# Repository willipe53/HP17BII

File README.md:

# HP17BII

This is a project done to test several microcontrollers by using them to replace the innards of an HP 17BII business calculator with several new functions, such as Space Invaders game, a piano, and yes of course also hand-coded calculator. 

All attempts are included here.  Probably the most complete version is [HP17B41.ino](HP17B41/HP17B41.ino), though it might take a little work to get any of these to compile at this point.  I only make public because others may wish to replicate some of the functionality below.

`#define PIANO_MODE` renders a piano on the display, then plays notes on the HP's piezo buzzer.  The buzzer is connected to an analog pin, and when a piano key is pressed, the desired frequemcy is tossed into an array (two arrays actually: `toneStart[]` for the start time in millis and `toneFreq[]` for the frequency) to be read and played by the main loop.

`#define GAME_MODE` is the Space Invaders game.  If I come back to this, I'll probably make it a lot more object-oriented.  This version is anything but that.  It relies on a lot of global variables such as `goingLeft`, `goingRight`, `gunX`, `gunY`, `alienX`, `alienY`, and others to figure out where to place the gun and the aliens, whether a bullet has been fired, and the state of the barriers that the gun hides behind.  The hard work is done in a function called `drawPlayArea()` that is called by the main loop.
   
`#define CALC_MODE` is the default mode, the calculator.  It is a bit over-engineered with a really hard to understand function pointer array which is called by main: 

`(*fcns[key][currentMode]) (key);` 

whenever a key press event is detected by the `<Keypad.h>` library.  

Most of this code needs to be rewritten, to be honest.  I only make this project public because there may be useful code snippets for people challenging themselves with similar microcontroller display and sound challenges.

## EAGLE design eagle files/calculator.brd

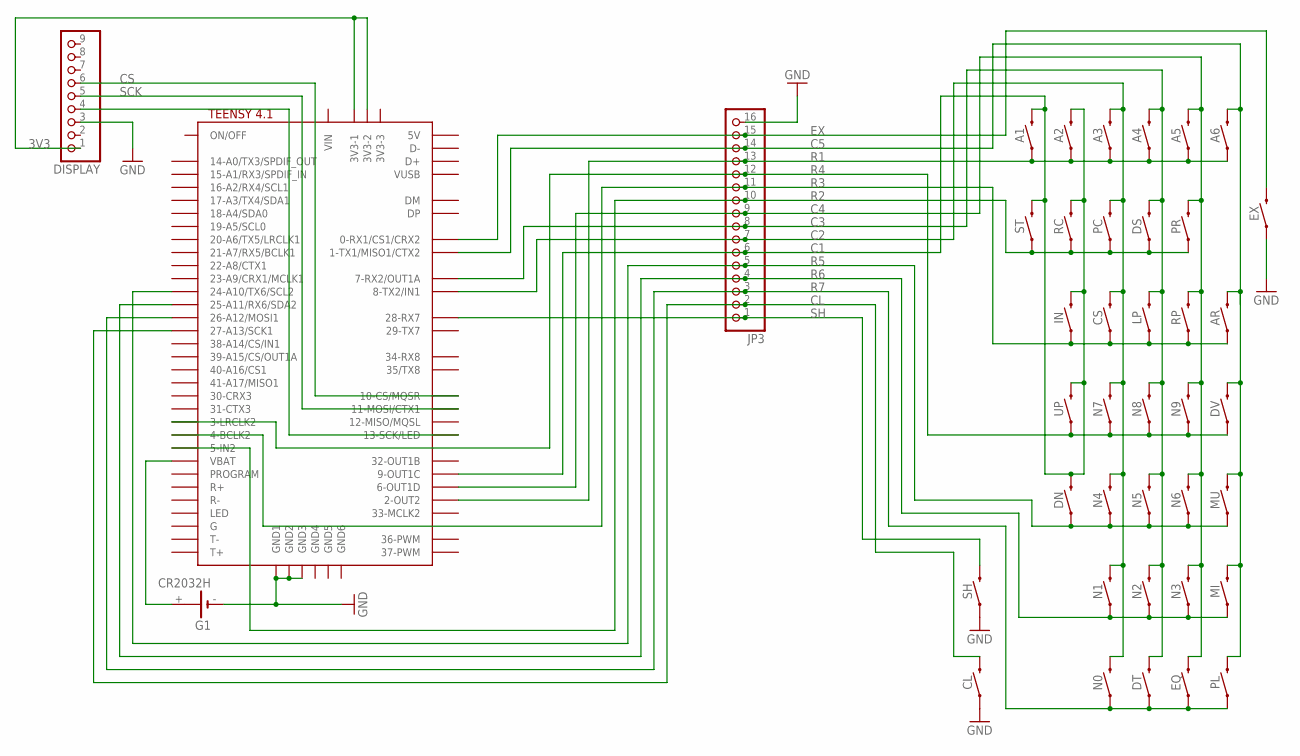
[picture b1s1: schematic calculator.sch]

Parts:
A1, A2, A3, A4, A5, A6: MOMENTARY-SWITCH-SPST-PTH-6.0MM; TACTILE_SWITCH_PTH_6.0MM
AR: MOMENTARY-SWITCH-SPST-PTH-6.0MM; TACTILE_SWITCH_PTH_6.0MM
CL: MOMENTARY-SWITCH-SPST-PTH-6.0MM; TACTILE_SWITCH_PTH_6.0MM
CS: MOMENTARY-SWITCH-SPST-PTH-6.0MM; TACTILE_SWITCH_PTH_6.0MM
DISPLAY: PINHD-1X9; 1X09-BIG
DN: MOMENTARY-SWITCH-SPST-PTH-6.0MM; TACTILE_SWITCH_PTH_6.0MM
DS: MOMENTARY-SWITCH-SPST-PTH-6.0MM; TACTILE_SWITCH_PTH_6.0MM
DT: MOMENTARY-SWITCH-SPST-PTH-6.0MM; TACTILE_SWITCH_PTH_6.0MM
DV: MOMENTARY-SWITCH-SPST-PTH-6.0MM; TACTILE_SWITCH_PTH_6.0MM
EQ: MOMENTARY-SWITCH-SPST-PTH-6.0MM; TACTILE_SWITCH_PTH_6.0MM
EX: MOMENTARY-SWITCH-SPST-PTH-6.0MM; TACTILE_SWITCH_PTH_6.0MM
G1: CR2032H
IN: MOMENTARY-SWITCH-SPST-PTH-6.0MM; TACTILE_SWITCH_PTH_6.0MM
JP3: PINHD-1X16; 1X16
LP: MOMENTARY-SWITCH-SPST-PTH-6.0MM; TACTILE_SWITCH_PTH_6.0MM
MI: MOMENTARY-SWITCH-SPST-PTH-6.0MM; TACTILE_SWITCH_PTH_6.0MM
MU: MOMENTARY-SWITCH-SPST-PTH-6.0MM; TACTILE_SWITCH_PTH_6.0MM
N0, N1, N2, N3, N4, N5, N6, N7, N8, N9: MOMENTARY-SWITCH-SPST-PTH-6.0MM; TACTILE_SWITCH_PTH_6.0MM
PC: MOMENTARY-SWITCH-SPST-PTH-6.0MM; TACTILE_SWITCH_PTH_6.0MM
PL: MOMENTARY-SWITCH-SPST-PTH-6.0MM; TACTILE_SWITCH_PTH_6.0MM
PR: MOMENTARY-SWITCH-SPST-PTH-6.0MM; TACTILE_SWITCH_PTH_6.0MM
RC: MOMENTARY-SWITCH-SPST-PTH-6.0MM; TACTILE_SWITCH_PTH_6.0MM
RP: MOMENTARY-SWITCH-SPST-PTH-6.0MM; TACTILE_SWITCH_PTH_6.0MM
SH: MOMENTARY-SWITCH-SPST-PTH-6.0MM; TACTILE_SWITCH_PTH_6.0MM
ST: MOMENTARY-SWITCH-SPST-PTH-6.0MM; TACTILE_SWITCH_PTH_6.0MM
U$1: TEENSY41
UP: MOMENTARY-SWITCH-SPST-PTH-6.0MM; TACTILE_SWITCH_PTH_6.0MM

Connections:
3V3: DISPLAY.1, U$1.3V3-1, U$1.3V3-2
C1: A1.3 (2), A2.3 (2), DN.3 (2), IN.3 (2), JP3.6, RC.3 (2), ST.3 (2), U$1.9-OUT1C, UP.3 (2)
C2: A3.3 (2), CS.3 (2), JP3.7, N0.3 (2), N1.3 (2), N4.3 (2), N7.3 (2), PC.3 (2), U$1.8-TX2/IN2 (8-TX2/IN1)
C3: A4.3 (2), DS.3 (2), DT.3 (2), JP3.8, LP.3 (2), N2.3 (2), N5.3 (2), N8.3 (2), U$1.7-RX2/OUT1A
C4: A5.3 (2), EQ.3 (2), JP3.9, N3.3 (2), N6.3 (2), N9.3 (2), PR.3 (2), RP.3 (2), U$1.6-OUT1D
C5: A6.3 (2), AR.3 (2), DV.3 (2), JP3.14, MI.3 (2), MU.3 (2), PL.3 (2), U$1.1-TX1/MISO1/CTX2
CL: CL.3 (2), JP3.2, U$1.27-A13/SCK1
CS: DISPLAY.6, U$1.10-CS\MQSR (10-CS/MQSR)
EX: EX.3 (2), JP3.15, U$1.0-RX1/CS1/CRX2
GND: CL.1, DISPLAY.3, EX.1, G1.-, JP3.16, SH.1, U$1.GND1, U$1.GND2, U$1.GND3
MOSI: DISPLAY.5, U$1.11-MOSI/CTX1
unnamed: G1.+, U$1.VBAT
R1: A1.1, A2.1, A3.1, A4.1, A5.1, A6.1, JP3.13, U$1.2-OUT2
R2: DS.1, JP3.10, PC.1, PR.1, RC.1, ST.1, U$1.5-IN2
R3: AR.1, CS.1, IN.1, JP3.11, LP.1, RP.1, U$1.4-BCLK2
R4: DV.1, JP3.12, N7.1, N8.1, N9.1, U$1.3-LRCLK2, UP.1
R5: DN.1, JP3.5, MU.1, N4.1, N5.1, N6.1, U$1.24-A10/TX6/SCL2
R6: JP3.4, MI.1, N1.1, N2.1, N3.1, U$1.25-A11/RX6/SDA2
R7: DT.1, EQ.1, JP3.3, N0.1, PL.1, U$1.26-A12/MOSI1
SCK: DISPLAY.4, U$1.13-SCK/LED
SH: JP3.1, SH.3 (2), U$1.28-RX7

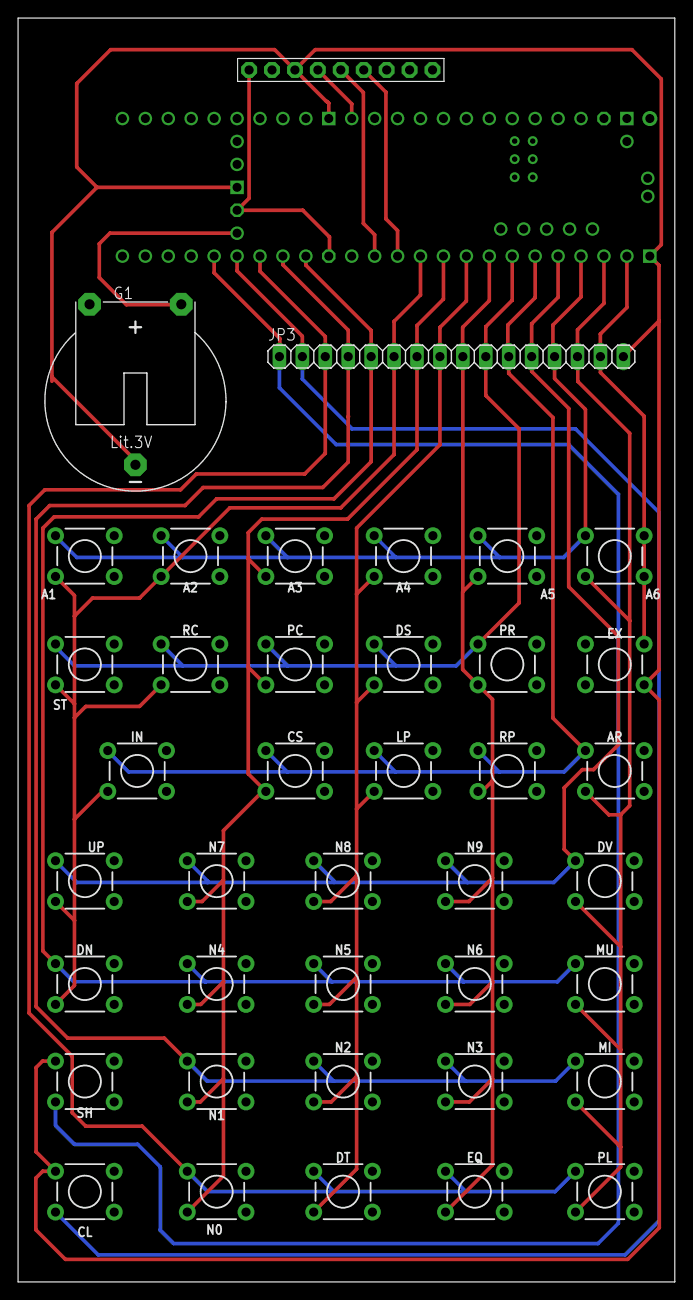
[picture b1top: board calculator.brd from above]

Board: 2 copper layers, 72.8 x 140.0 mm, 41 parts (1 on the bottom side), 21 nets.

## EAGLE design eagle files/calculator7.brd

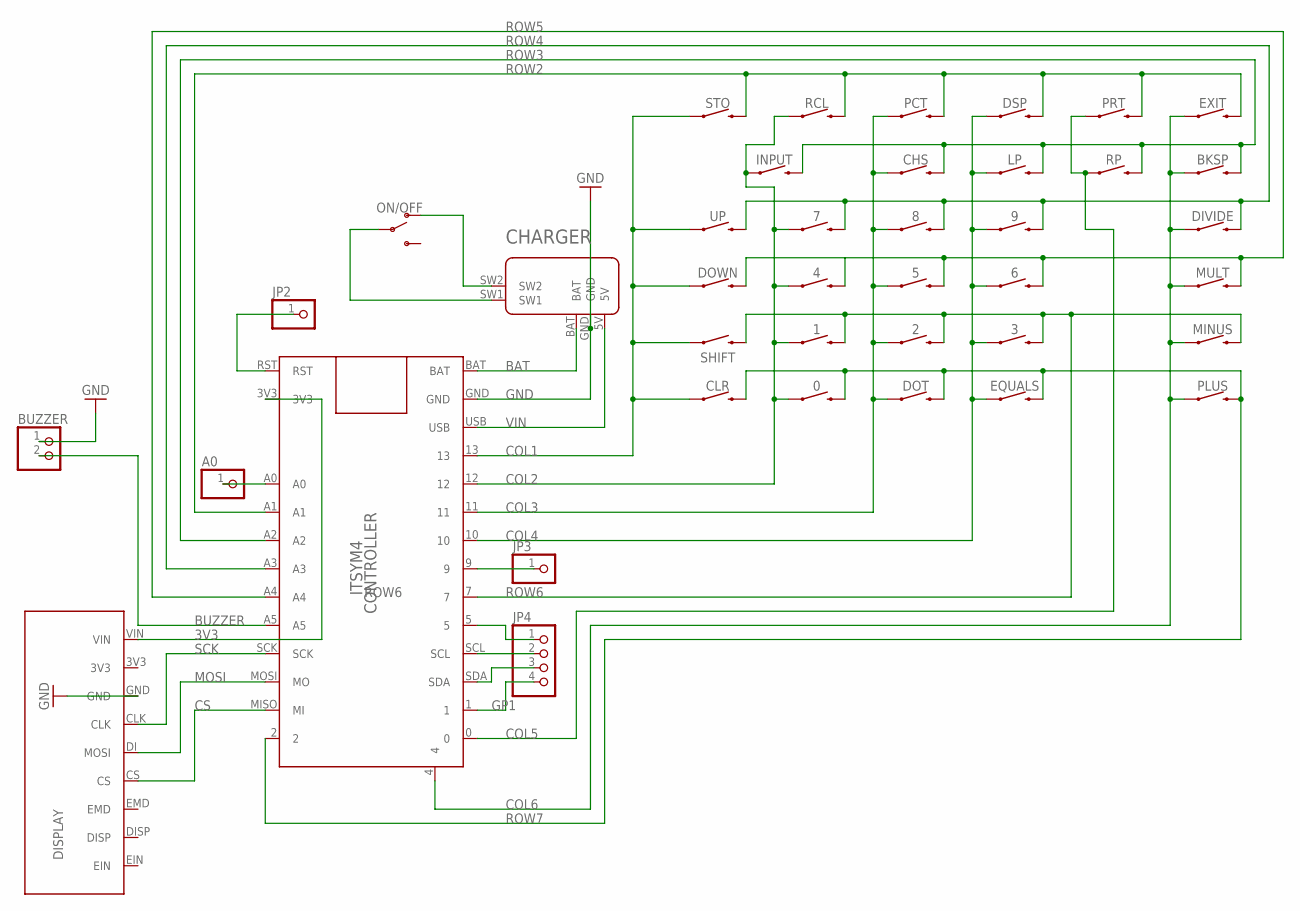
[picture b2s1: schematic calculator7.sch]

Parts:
0, 1, 2, 3, 4, 5, 6, 7, 8, 9: 3BUTTON
A0: PINHD-1X1; 1X01
BKSP: 3BUTTON
BUZZER: PINHD-1X2; 1X02
CHARGER: LIPO_BACKPACK
CHS: 3BUTTON
CLR: 3BUTTON
CONTROLLER: ITSYM4
DISPLAY: SHARPMEM_FULL
DIVIDE: 3BUTTON
DOT: 3BUTTON
DOWN: 3BUTTON
DSP: 3BUTTON
EQUALS: 3BUTTON
EXIT: 3BUTTON
INPUT: 3BUTTON
JP2, JP3: PINHD-1X1; 1X01
JP4: PINHD-1X4; 1X04
LP: 3BUTTON
MINUS: 3BUTTON
MULT: 3BUTTON
ON/OFF: LIL_SWITCH
PCT: 3BUTTON
PLUS: 3BUTTON
PRT: 3BUTTON
RCL: 3BUTTON
RP: 3BUTTON
SHIFT: 3BUTTON
STO: 3BUTTON
UP: 3BUTTON

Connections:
3V3: CONTROLLER.3V3, DISPLAY.VIN
A0: A0.1, CONTROLLER.A0
BAT: CHARGER.BAT, CONTROLLER.BAT
BUZZER: BUZZER.2, CONTROLLER.A5
COL1: CLR.P1 (1), CONTROLLER.13, DOWN.P1 (1), SHIFT.P1 (1), STO.P1 (1), UP.P1 (1)
COL2: 0.P1 (1), 1.P1 (1), 4.P1 (1), 7.P1 (1), CONTROLLER.12, INPUT.P1 (1), RCL.P1 (1)
COL3: 2.P1 (1), 5.P1 (1), 8.P1 (1), CHS.P1 (1), CONTROLLER.11, DOT.P1 (1), PCT.P1 (1)
COL4: 3.P1 (1), 6.P1 (1), 9.P1 (1), CONTROLLER.10, DSP.P1 (1), EQUALS.P1 (1), LP.P1 (1)
COL5: CONTROLLER.0, PRT.P1 (1), RP.P1 (1)
COL6: BKSP.P1 (1), CONTROLLER.4, DIVIDE.P1 (1), EXIT.P1 (1), MINUS.P1 (1), MULT.P1 (1), PLUS.P1 (1)
CS: CONTROLLER.MISO (MI), DISPLAY.CS
GND: BUZZER.1, CHARGER.GND, CONTROLLER.GND, DISPLAY.GND
GP1: CONTROLLER.1, JP4.4
GP5: CONTROLLER.5, JP4.1
GP9: CONTROLLER.9, JP3.1
MOSI: CONTROLLER.MOSI (MO), DISPLAY.DI (MOSI)
unnamed: CHARGER.SW1, ON/OFF.COM
unnamed: CHARGER.SW2, ON/OFF.P1
ROW2: CONTROLLER.A1, DSP.P2 (2), EXIT.P2 (2), PCT.P2 (2), PRT.P2 (2), RCL.P2 (2), STO.P2 (2)
ROW3: BKSP.P2 (2), CHS.P2 (2), CONTROLLER.A2, INPUT.P2 (2), LP.P2 (2), RP.P2 (2)
ROW4: 7.P2 (2), 8.P2 (2), 9.P2 (2), CONTROLLER.A3, DIVIDE.P2 (2), UP.P2 (2)
ROW5: 4.P2 (2), 5.P2 (2), 6.P2 (2), CONTROLLER.A4, DOWN.P2 (2), MULT.P2 (2)
ROW6: 1.P2 (2), 2.P2 (2), 3.P2 (2), CONTROLLER.7, MINUS.P2 (2), SHIFT.P2 (2)
ROW7: 0.P2 (2), CLR.P2 (2), CONTROLLER.2, DOT.P2 (2), EQUALS.P2 (2), PLUS.P2 (2)
RST: CONTROLLER.RST, JP2.1
SCK: CONTROLLER.SCK, DISPLAY.CLK
SCL: CONTROLLER.SCL, JP4.2
SDA: CONTROLLER.SDA, JP4.3
VIN: CHARGER.5V, CONTROLLER.USB

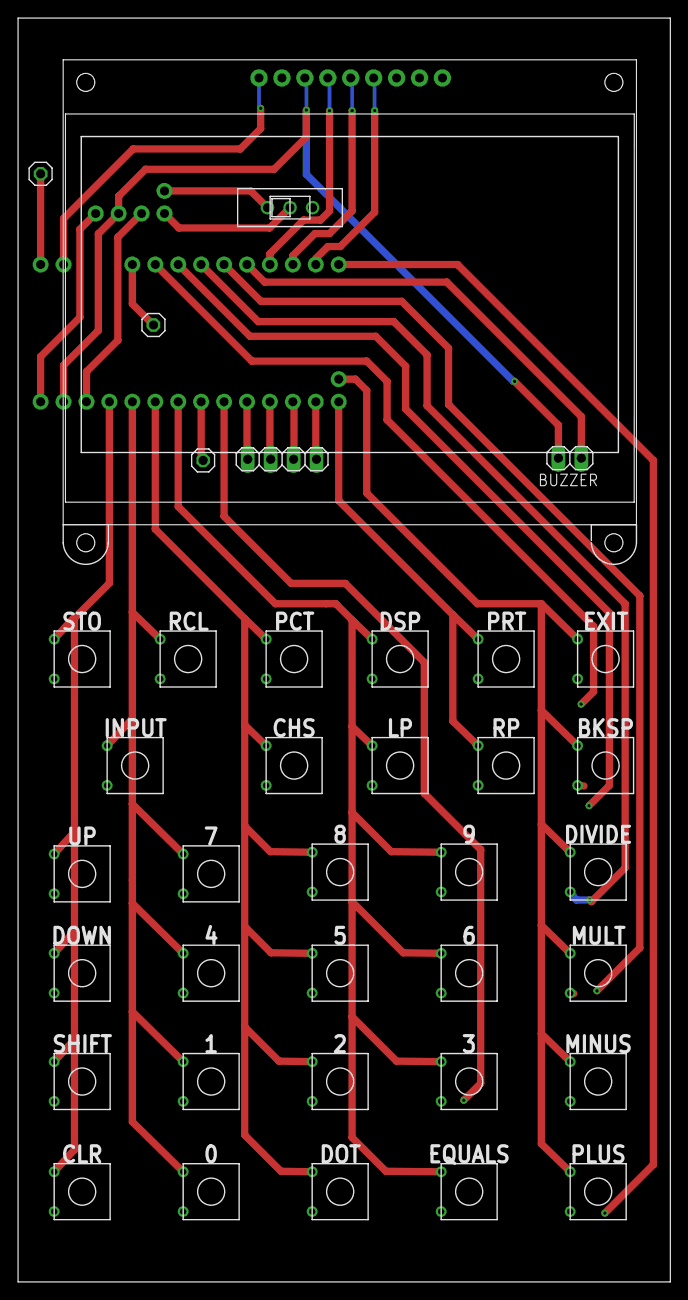
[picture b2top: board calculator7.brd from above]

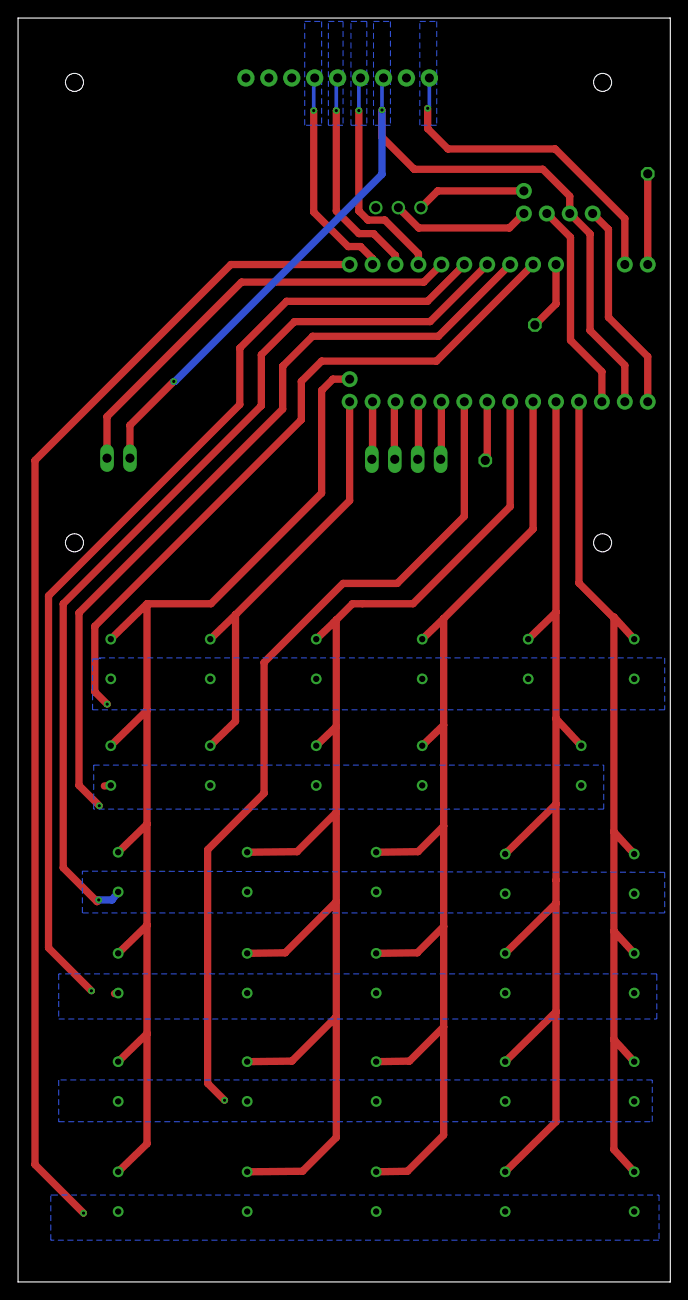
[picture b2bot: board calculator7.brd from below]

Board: 2 copper layers, 72.2 x 140.0 mm, 40 parts (2 on the bottom side), 29 nets.

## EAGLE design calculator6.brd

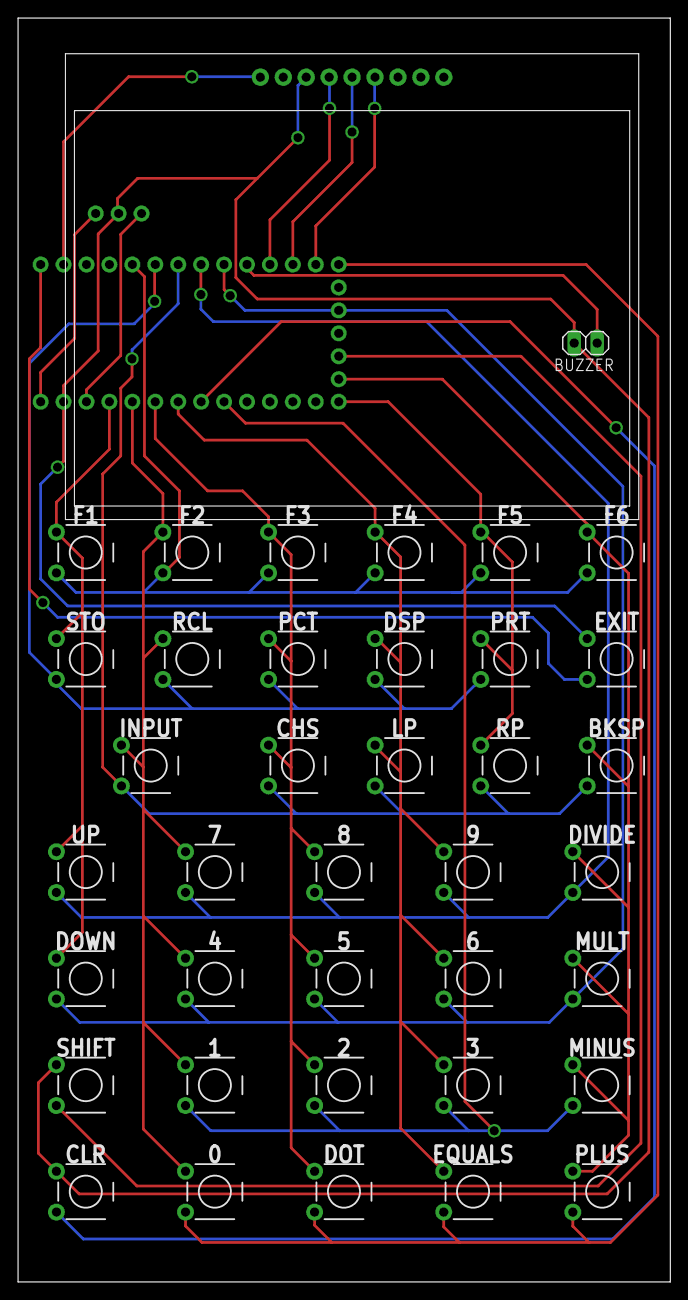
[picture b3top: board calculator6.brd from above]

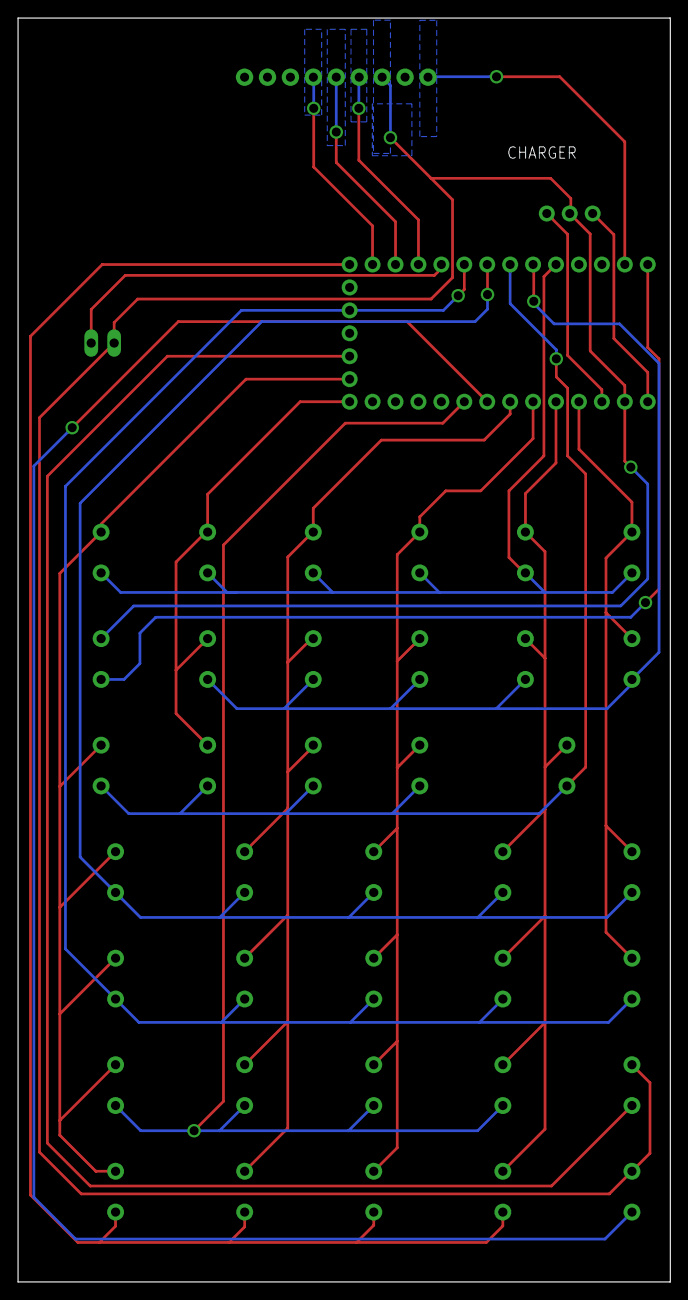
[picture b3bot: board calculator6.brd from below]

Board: 2 copper layers, 72.2 x 140.0 mm, 41 parts (2 on the bottom side), 24 nets.

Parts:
0, 1, 2, 3, 4, 5, 6, 7, 8, 9: BUTTON
BKSP: BUTTON
BUZZER: 1X02
CHARGER: LIPO_BACKPACK
CHS: BUTTON
CLR: BUTTON
CONTROLLER: ITSYM4
DIVIDE: BUTTON
DOT: BUTTON
DOWN: BUTTON
DSP: BUTTON
EQUALS: BUTTON
EXIT: BUTTON
F1, F2, F3, F4, F5, F6: BUTTON
INPUT: BUTTON
LP: BUTTON
MINUS: BUTTON
MULT: BUTTON
PCT: BUTTON
PLUS: BUTTON
PRT: BUTTON
RCL: BUTTON
RP: BUTTON
SHARPMEM: SHARPMEM
SHIFT: BUTTON
STO: BUTTON
UP: BUTTON

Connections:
3V3: CONTROLLER.3V3, SHARPMEM.VIN
BAT: CHARGER.BAT, CONTROLLER.BAT
BUZZER: BUZZER.2, CONTROLLER.A5
CLEAR: CLR.3, CONTROLLER.9
COL1: CONTROLLER.13, DOWN.1, F1.1, STO.1, UP.1
COL2: 0.1, 1.1, 4.1, 7.1, CONTROLLER.12, F2.1, INPUT.1, RCL.1
COL3: 2.1, 5.1, 8.1, CHS.1, CONTROLLER.11, DOT.1, F3.1, PCT.1
COL4: 3.1, 6.1, 9.1, CONTROLLER.10, DSP.1, EQUALS.1, F4.1, LP.1
COL5: CONTROLLER.0, F5.1, PRT.1, RP.1
COL6: BKSP.1, CONTROLLER.4, DIVIDE.1, F6.1, MINUS.1, MULT.1, PLUS.1
CS: CONTROLLER.MISO, SHARPMEM.CS
EXIT: CONTROLLER.RST, EXIT.3
GND: BUZZER.1, CHARGER.GND, CLR.1, CONTROLLER.GND, EXIT.1, SHARPMEM.GND, SHIFT.1
MOSI: CONTROLLER.MOSI, SHARPMEM.DI
ROW1: CONTROLLER.A0, F1.3, F2.3, F3.3, F4.3, F5.3, F6.3
ROW2: CONTROLLER.A1, DSP.3, PCT.3, PRT.3, RCL.3, STO.3
ROW3: BKSP.3, CHS.3, CONTROLLER.A2, INPUT.3, LP.3, RP.3
ROW4: 7.3, 8.3, 9.3, CONTROLLER.A3, DIVIDE.3, UP.3
ROW5: 4.3, 5.3, 6.3, CONTROLLER.A4, DOWN.3, MULT.3
ROW6: 1.3, 2.3, 3.3, CONTROLLER.7, MINUS.3
ROW7: 0.3, CONTROLLER.2, DOT.3, EQUALS.3, PLUS.3
SCK: CONTROLLER.SCK, SHARPMEM.CLK
SHIFT: CONTROLLER.3, SHIFT.3
VIN: CHARGER.5V, CONTROLLER.USB

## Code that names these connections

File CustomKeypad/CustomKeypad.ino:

/* @file CustomKeypad.pde
|| @version 1.0
|| @author Alexander Brevig
|| @contact alexanderbrevig@gmail.com
||
|| @description
|| | Demonstrates changing the keypad size and key values.
|| #
*/
#include <Keypad.h>

#define EXIT   2
#define CLEAR 20
#define SHIFT 12
#define ROWS   3 
#define COLS   10
 
char keys[ROWS][COLS] = {
  {'E','b','c','d','e','f','g','h','i','j'},
  {'k','l','m','n','o','p','q','r','s','C'},
  {'u','v','w','x','y','z','1','2','3','4'}
};
byte rowPins[ROWS] = {23,22,21}; 
byte colPins[COLS] = {20,19,18,17,16,15,14,13,12,11}; 

bool exitPressed = false;
bool clearPressed = false;
bool shiftPressed = false;

Keypad customKeypad = Keypad( makeKeymap(keys), rowPins, colPins, ROWS, COLS); 


void(* resetFunc) (void) = 0;//declare reset function at address 0

void clearFunc() { Serial.println("User pressed clear."); }

void shiftFunc() { Serial.println("User pressed shift."); }

void setup(){
  Serial.begin(115200);
  pinMode(EXIT, INPUT_PULLUP);
  pinMode(CLEAR, INPUT_PULLUP);
  pinMode(SHIFT, INPUT_PULLUP);
  
  while (!(Serial)) {}
  Serial.println("AWAKE!");

//  for (int i=0; i<ROWS; i++) {
//   pinMode(rowPins[i], INPUT);
//  }
//  for (int i=0; i<COLS; i++) {
//   pinMode(colPins[i], INPUT);
//  }
}
  
void loop(){
  char customKey = customKeypad.getKey();
  // if (digitalRead(EXIT) == 0) resetFunc();
  // if (digitalRead(CLEAR) == 0) clearFunc();
  // if (digitalRead(SHIFT) == 0) shiftFunc();  
  if (customKey){
    Serial.printf("KEY: %c (%d)\n", customKey, customKey);
  }
  
//resetFunc(); //call reset
}

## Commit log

2022-04-05 for travel
2022-04-09 Using 32 board
2022-04-12 Somewhat working
2022-04-15 Pins confirmed
2022-04-16 Working keyboard with LC
2022-04-19 Working pins
2022-04-21 Function pointer array works
2022-04-25 Display offsets configured
2022-05-02 Mod button logic implemented
2022-10-10 Updated documentation
2024-11-17 Put aside for a while

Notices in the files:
parts and their libraries:
SparkFun-Switches: Licensing: Creative Commons ShareAlike 4.0 International - https://creativecommons.org/licenses/by-sa/4.0
